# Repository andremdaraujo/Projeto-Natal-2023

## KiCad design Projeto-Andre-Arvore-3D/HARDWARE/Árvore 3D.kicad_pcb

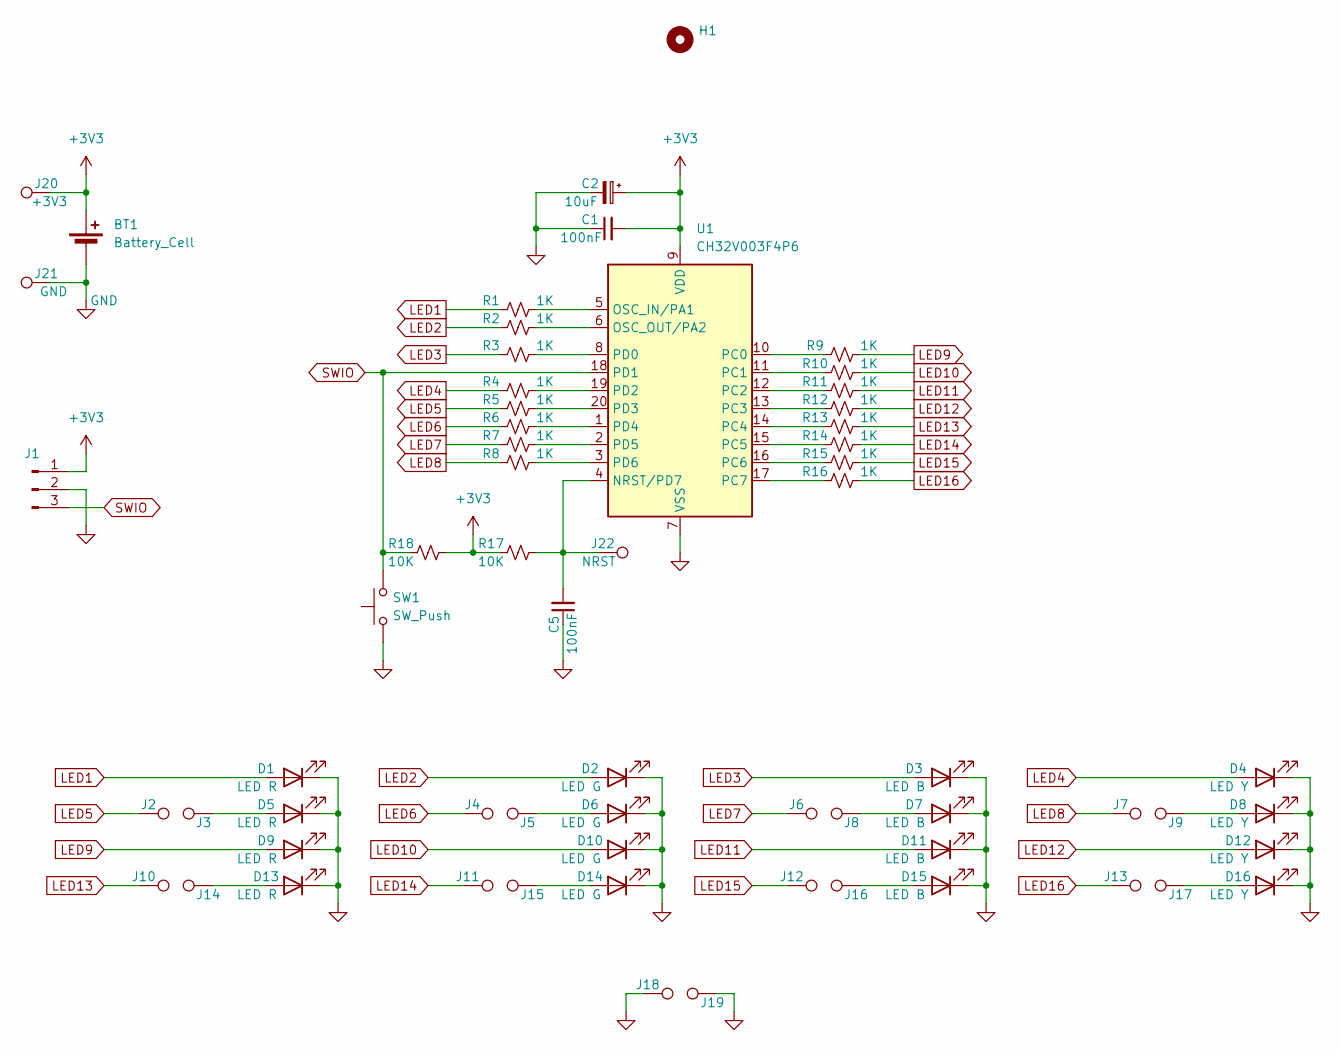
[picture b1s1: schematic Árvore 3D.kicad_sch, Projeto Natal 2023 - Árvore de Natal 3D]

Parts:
BT1: Battery_Cell; BatteryHolder_Keystone_3002_1x2032
C1, C5: 100nF; C_0603_1608Metric_Pad1.08x0.95mm_HandSolder
C2: 10uF; C_0805_2012Metric_Pad1.18x1.45mm_HandSolder
D1, D5, D9, D13: LED R; LED_D5.0mm
D2, D6, D10, D14: LED G; LED_D5.0mm
D3, D7, D11, D15: LED B; LED_D5.0mm
D4, D8, D12, D16: LED Y; LED_D5.0mm
H1: MountingHole; MountingHole_2.5mm_Pad_Via
J1: Conn_01x03_Pin; PinHeader_1x03_P2.54mm_Vertical
J2, J3, J4, J5, J6, J7, J8, J9, J10, J11, J12, J13, J14, J15, J16, J17, J18, J19: TestPoint; TestPoint_Pad_D2.5mm
J20: +3V3; TestPoint_THTPad_D1.5mm_Drill0.7mm
J21: GND; TestPoint_THTPad_D1.5mm_Drill0.7mm
J22: NRST; TestPoint_THTPad_D1.5mm_Drill0.7mm
R1, R2, R3, R4, R5, R6, R7, R8, R9, R10, R11, R12, R13, R14, R15, R16: 1K; R_0603_1608Metric_Pad0.98x0.95mm_HandSolder
R17, R18: 10K; R_0603_1608Metric_Pad0.98x0.95mm_HandSolder
SW1: SW_Push; SW_Push_1P1T_NO_CK_KSC6xxJ
U1: CH32V003F4P6; TSSOP-20_4.4x6.5mm_P0.65mm

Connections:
+3V3: BT1.1 (+), C1.2, C2.1, J1.1, J20.1, R17.1, R18.2, U1.9 (VDD)
GND: BT1.2 (-), C1.1, C2.2, C5.1, D1.1 (K), D2.1 (K), D3.1 (K), D4.1 (K), D5.1 (K), D6.1 (K), D7.1 (K), D8.1 (K), D9.1 (K), D10.1 (K), D11.1 (K), D12.1 (K), D13.1 (K), D14.1 (K), D15.1 (K), D16.1 (K), J1.2, J18.1, J19.1, J21.1, SW1.1, U1.7 (VSS)
LED1: D1.2 (A), R1.1
LED2: D2.2 (A), R2.1
LED3: D3.2 (A), R3.1
LED4: D4.2 (A), R4.1
LED5: J2.1, R5.1
LED6: J4.1, R6.1
LED7: J6.1, R7.1
LED8: J7.1, R8.1
LED9: D9.2 (A), R9.2
LED10: D10.2 (A), R10.2
LED11: D11.2 (A), R11.2
LED12: D12.2 (A), R12.2
LED13: J10.1, R13.2
LED14: J11.1, R14.2
LED15: J12.1, R15.2
LED16: J13.1, R16.2
unnamed: D5.2 (A), J3.1
unnamed: D6.2 (A), J5.1
unnamed: D7.2 (A), J8.1
unnamed: D8.2 (A), J9.1
unnamed: D13.2 (A), J14.1
unnamed: D14.2 (A), J15.1
unnamed: D15.2 (A), J16.1
unnamed: D16.2 (A), J17.1
unnamed: C5.2, J22.1, R17.2, U1.4 (NRST/PD7)
unnamed: R1.2, U1.5 (OSC_IN/PA1)
unnamed: R2.2, U1.6 (OSC_OUT/PA2)
unnamed: R9.1, U1.10 (PC0)
unnamed: R10.1, U1.11 (PC1)
unnamed: R11.1, U1.12 (PC2)
unnamed: R12.1, U1.13 (PC3)
unnamed: R13.1, U1.14 (PC4)
unnamed: R14.1, U1.15 (PC5)
unnamed: R15.1, U1.16 (PC6)
unnamed: R16.1, U1.17 (PC7)
unnamed: R3.2, U1.8 (PD0)
unnamed: R4.2, U1.19 (PD2)
unnamed: R5.2, U1.20 (PD3)
unnamed: R6.2, U1.1 (PD4)
unnamed: R7.2, U1.2 (PD5)
unnamed: R8.2, U1.3 (PD6)
SWIO: J1.3, R18.1, SW1.2, U1.18 (PD1)

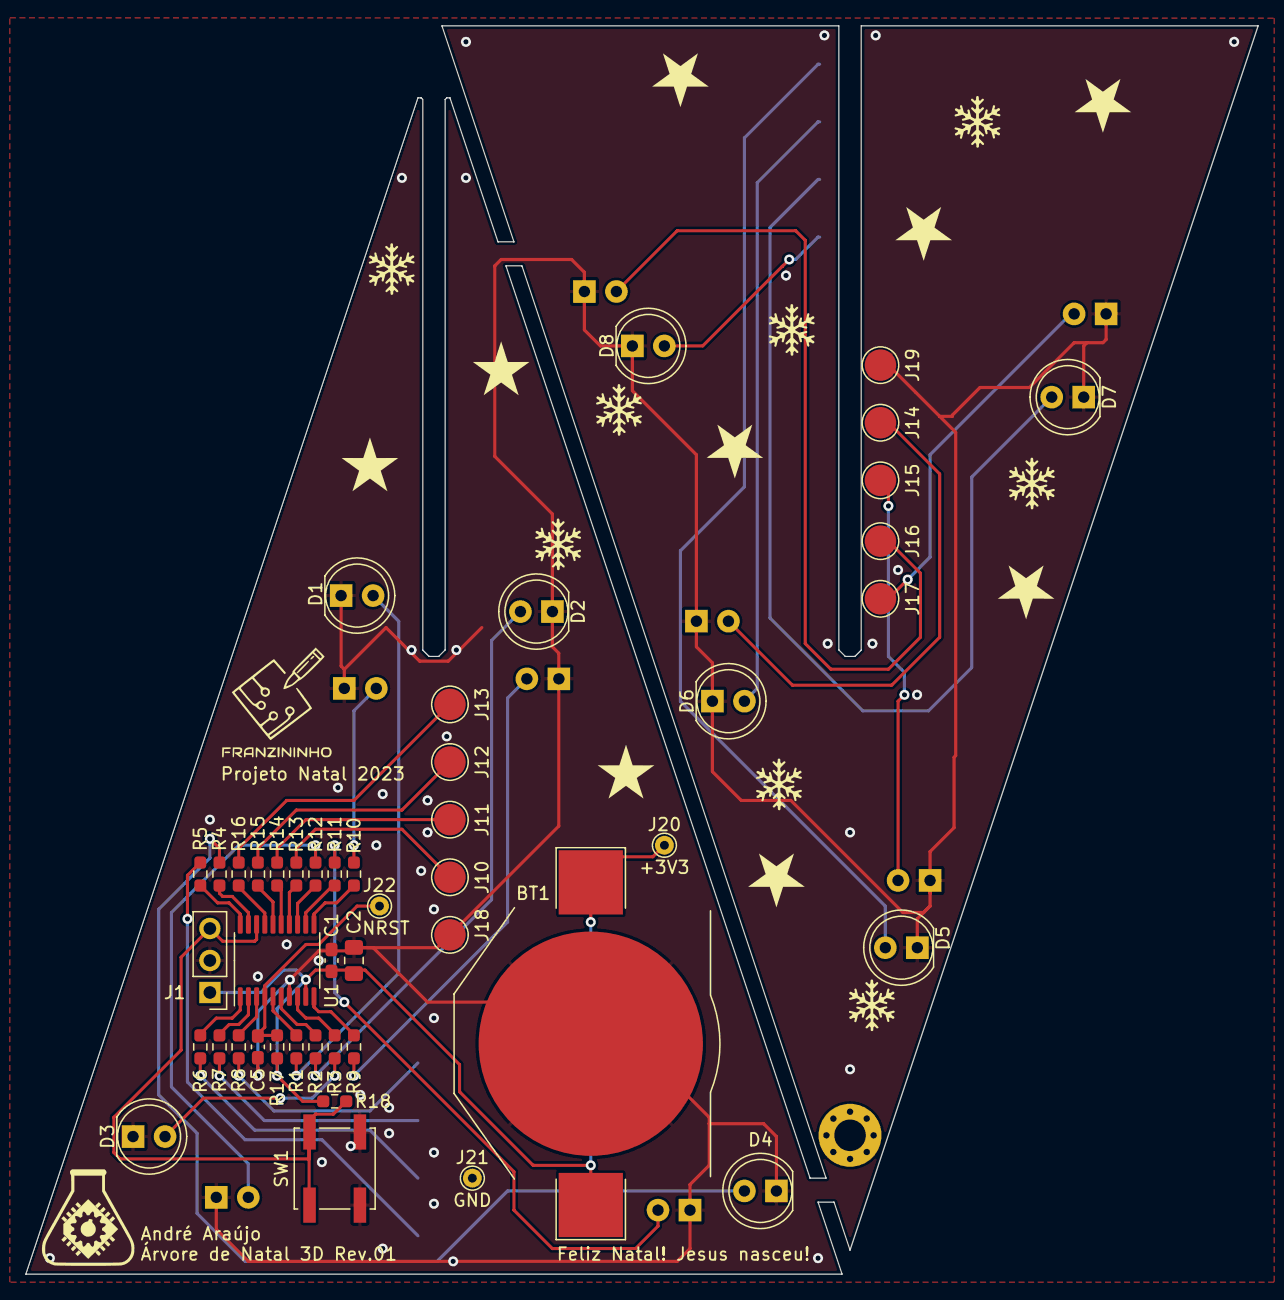
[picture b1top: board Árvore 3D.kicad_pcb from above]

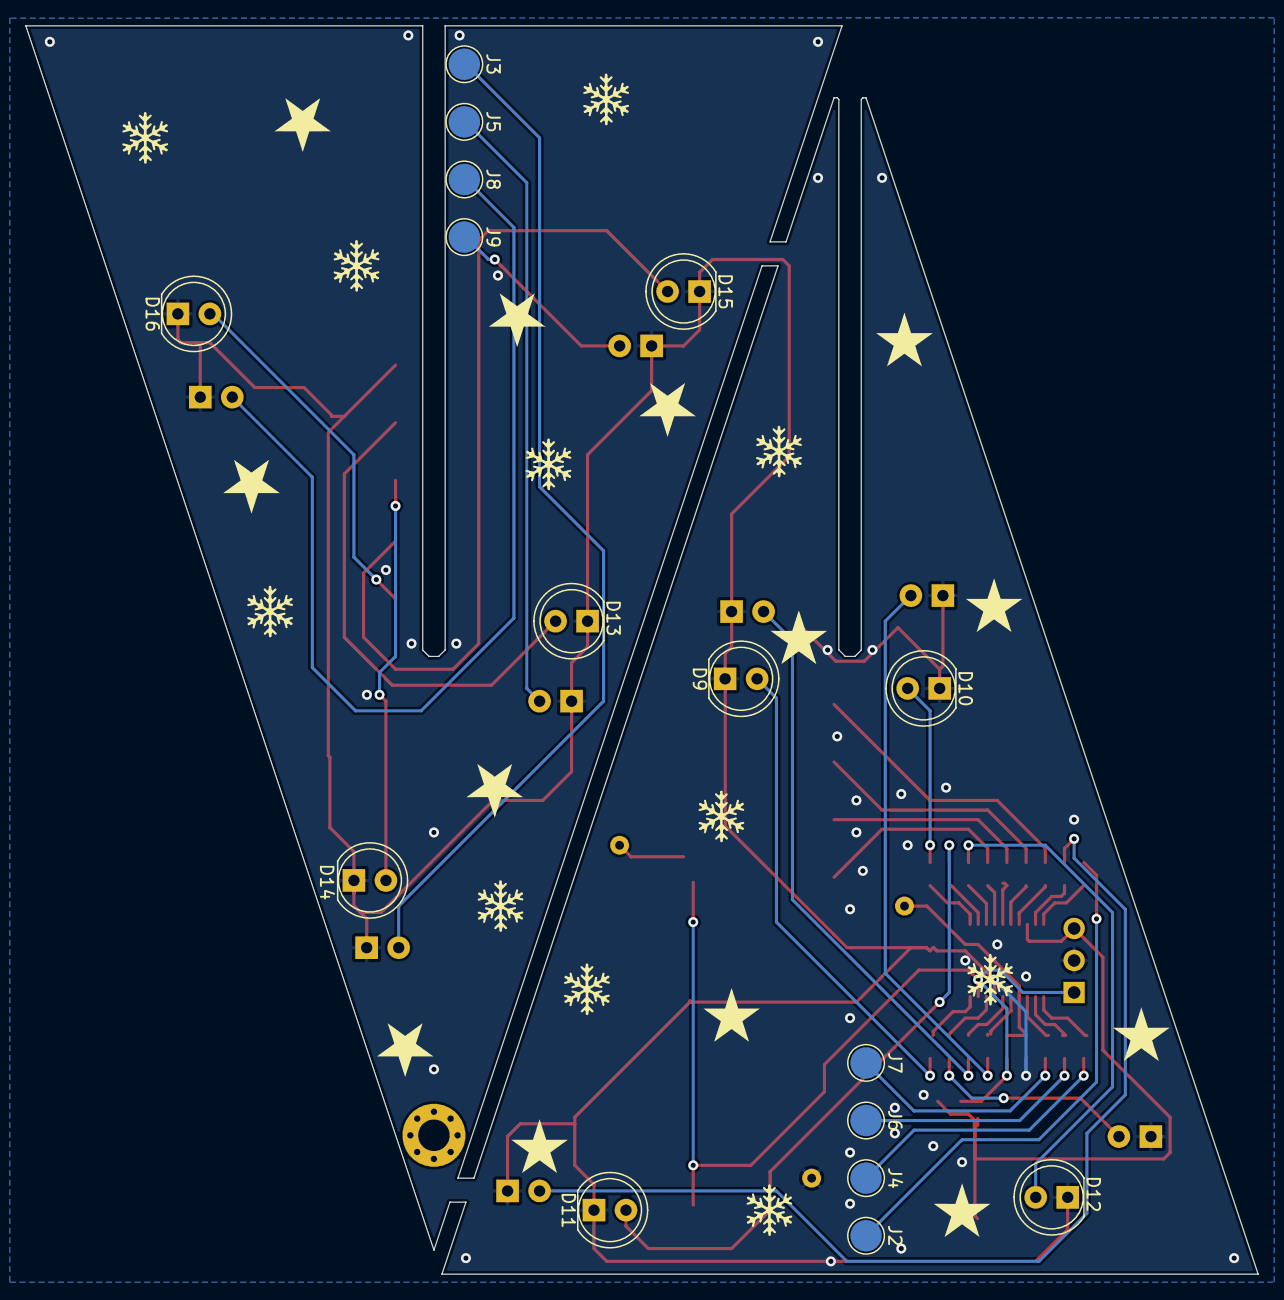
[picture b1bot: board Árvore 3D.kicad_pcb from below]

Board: 2 copper layers, 97.8 x 99.1 mm, 63 parts (16 on the bottom side), 44 nets.

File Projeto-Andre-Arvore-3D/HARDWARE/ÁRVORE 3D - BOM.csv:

"Id","Designator","Footprint","Quantity","Designation","Supplier and ref",
1,"J16,J10,J18,J15,J11,J12,J14,J17,J19,J13,J9,J7,J6,J8,J4,J2,J3,J5","TestPoint_Pad_D2.5mm",18,"TestPoint",,,
2,"R17,R18","R_0603_1608Metric_Pad0.98x0.95mm_HandSolder",2,"10K",,,
3,"D1,D5,D13,D9","LED_D5.0mm",4,"LED R",,,
4,"R15,R11,R16,R8,R4,R13,R6,R1,R12,R5,R2,R3,R7,R9,R10,R14","R_0603_1608Metric_Pad0.98x0.95mm_HandSolder",16,"1K",,,
5,"D3,D7,D15,D11","LED_D5.0mm",4,"LED B",,,
6,"C1,C5","C_0603_1608Metric_Pad1.08x0.95mm_HandSolder",2,"100nF",,,
7,"BT1","BatteryHolder_Keystone_3002_1x2032",1,"Battery_Cell",,,
8,"J22","TestPoint_THTPad_D1.5mm_Drill0.7mm",1,"NRST",,,
9,"D8,D4,D12,D16","LED_D5.0mm",4,"LED Y",,,
10,"D2,D6,D14,D10","LED_D5.0mm",4,"LED G",,,
11,"SW1","SW_Push_1P1T_NO_CK_KSC6xxJ",1,"SW_Push",,,
12,"J1","PinHeader_1x03_P2.54mm_Vertical",1,"Conn_01x03_Pin",,,
13,"C2","C_0805_2012Metric_Pad1.18x1.45mm_HandSolder",1,"10uF",,,
14,"U1","TSSOP-20_4.4x6.5mm_P0.65mm",1,"CH32V003F4P6",,,
15,"J21","TestPoint_THTPad_D1.5mm_Drill0.7mm",1,"GND",,,
16,"J20","TestPoint_THTPad_D1.5mm_Drill0.7mm",1,"+3V3",,,
17,"H1","MountingHole_2.5mm_Pad_Via",1,"MountingHole",,,

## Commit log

2023-11-18 Desenvolvimento do circuito e layout da Arvore 3D.
2023-11-18 Revisão do projeto e inclusão de logos.
2023-11-18 Finalização da versão inicial - Rev.00
2023-11-18 Inclusão de pasta com imagens utilizadas.
2023-11-20 Início da Rev.01. Inclusão de Test Points. Inclusão de botão e inclusão do arquivo 3D do suporte de bateria. Melhorias gerais.
2023-11-22 Finalização da Rev.01. Elaboração de arquivos de fabricação.
2023-12-21 Starting SW development.
2023-12-21 Restarting code - changed folder name and everything was messed up.
2023-12-21 Started a new program. Blinking ports C and D, but not A yet. Button and interrupt working, but not at the same time of debug.
2023-12-21 Now it is possible to control each color individually and turn all LEDs ON or OFF. Added LED map sheet.
2023-12-21 Created 2 animation modes and added standby mode. However after wakeup, mode is increased twice.
2023-12-23 Finished version 1.0 - AS IS!! :D
2024-03-01 Added shcematic in PDF format.
2024-03-01 Added photos.
2024-03-02 Added project costs spreadsheet.
2024-07-29 Added shcematic and layout PDFs. Added BOM sheet.
2024-07-29 Updated 3D models.
